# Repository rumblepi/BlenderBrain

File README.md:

# BlenderBrain

A controller for continuous flow blending of Nitrox and Trimix gases for diving.
The controller uses two oxygen sensors (one after Helium injection and one after Oxygen injection) and from this computes the composition of the resulting gas.
The desired mix can be adjusted by the user and is then automatically controlled via two magnetic valves. Depending on the currently measured mix, the valves are kept open longer or shorter. For this, a PI controller is implemented.

## Hardware

In the 'Hardware' folder, the KiCad files for the PCB are stored. Due to availability issues, the current configuration of the controller uses an Atmega168 microcontroller, but if available an Atmega328P can and should be used. The board requires two power supplies, one 5V to supply the microcontroller and operational amplifiers and a 24V to supply the magnetic valves as well as the indicator lights.

The oxygen sensors are assumed to be common rebreather sensors, namely ones similar to the NRC D-05R sensor range. These sensors expose three pins, of which we will use two to measure the output voltage. These galvanic cell sensors are dependent current sources outputting a given current for a certain oxygen partial pressure. The sensor also contains a small temperature compensation circuit with a few resistors and an NTC element, such that it effectively outputts a small voltage depending on the current oxygen partial pressure.
For more details see for example [http://www.advanceddivermagazine.com/articles/sensors/sensors.html].

As operational amplifiers, two TLC271 chips are used, but could be combined into a single TLC272 chip in the future. These OpAmps operate in non-inverting configuration with a gain of 101 and an additional feedback capacitor to filter high frequency noise. Note that only two of the three pins of the oxygen sensor are used.

### Programming the microcontroller via ISP

In-System-Programming can be used to update the firmware of the microcontroller. A detailed description of this procedure is given on the Arduino webpage (https://docs.arduino.cc/built-in-examples/arduino-isp/ArduinoISP), we store the most important points here for future reference.
We use an Arduino UNO in ISP mode to write to the Atmega microcontroller chip via the ISP pins on the board. 
Then, in the Arduino IDE the ISP sketch must be uploaded to the UNO via 'File->Examples->ArduinoISP->ArduinoISP'.

The ISP pins have a silkscreen overlay and the connections to the UNO are as follows: MOSI - 11, MISO - 12, SCK - 13, VCC - 5V, GND - GND, RESET - 10
In addition to this, it might be necessary to put a 10uF capacitor between the RESET and GND pins on the UNO.
The Atmega168 is available as processor of an Arduino Duemilanove, so in order to program it, select 'Tools->Board->Arduino Duemilanove or Dieciemila' and switch the processor to 'Atmega168' via 'Tools->Processor->Atmega168'. As we are using the UNO as an In-System-Programmer, also select 'Tools->Programmer->Arduino as ISP'. At first it might be necessary to burn a bootloader onto the chip, so select 'Tools->Burn Bootloader'. After that, the standard 'Upload'-button should do the trick.

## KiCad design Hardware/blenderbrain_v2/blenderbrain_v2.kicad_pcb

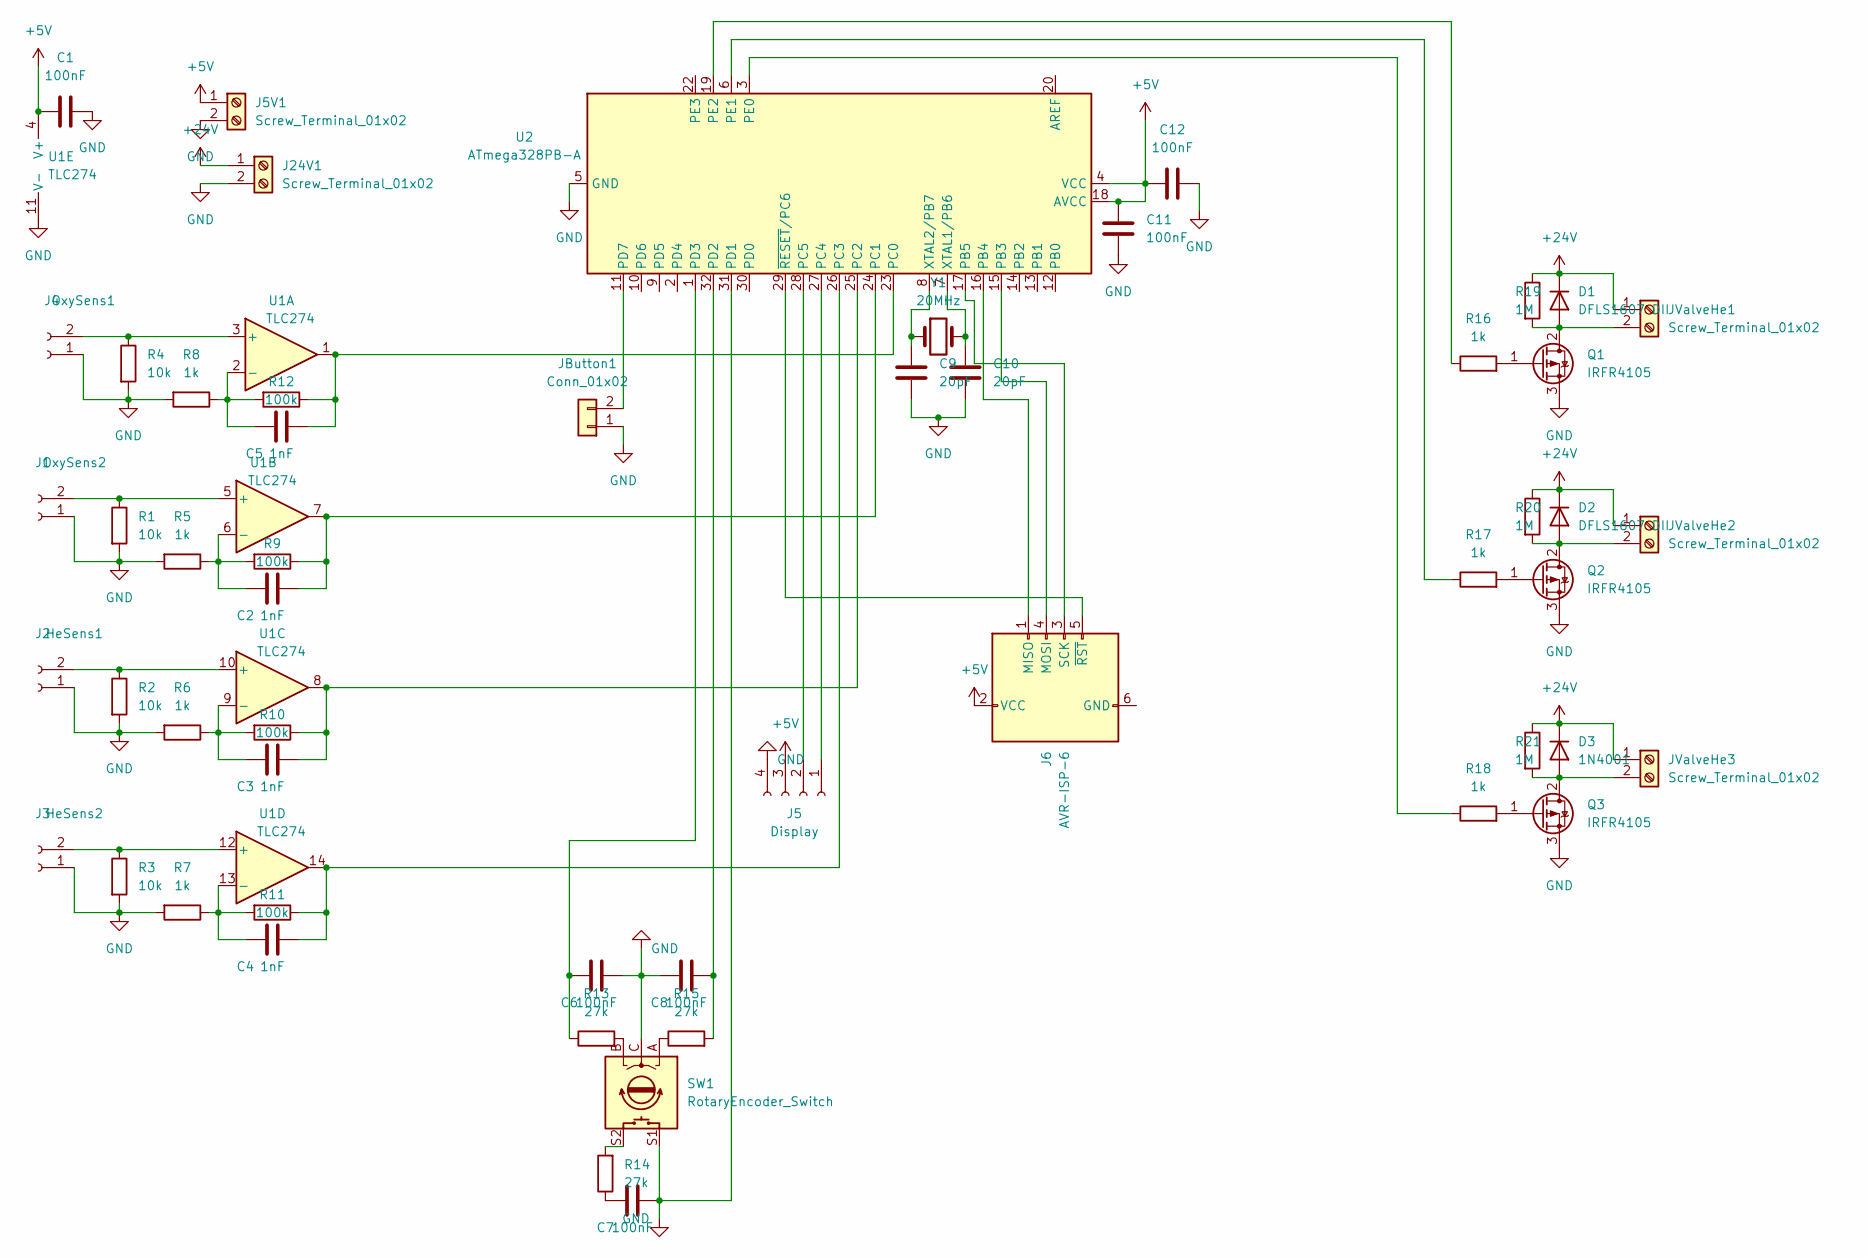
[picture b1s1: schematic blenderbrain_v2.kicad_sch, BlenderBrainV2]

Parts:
C1, C6, C7, C8, C11, C12: 100nF; C_1206_3216Metric
C2, C3, C4, C5: 1nF; C_1206_3216Metric
C9, C10: 20pF; C_1206_3216Metric
D1, D2: DFLS1607 DII; D_PowerDI-123
D3: 1N4001; D_PowerDI-123
J1: OxySens2; JST_EH_S2B-EH_1x02_P2.50mm_Horizontal
J2: HeSens1; JST_EH_S2B-EH_1x02_P2.50mm_Horizontal
J3: HeSens2; JST_EH_S2B-EH_1x02_P2.50mm_Horizontal
J4: OxySens1; JST_EH_S2B-EH_1x02_P2.50mm_Horizontal
J5: Display; PinSocket_1x04_P2.54mm_Vertical
J5V1, J24V1: Screw_Terminal_01x02; TerminalBlock_bornier-2_P5.08mm
J6: AVR-ISP-6; PinHeader_2x03_P2.54mm_Vertical
JButton1: Conn_01x02; PinHeader_1x02_P2.54mm_Vertical
JValveHe1, JValveHe2, JValveHe3: Screw_Terminal_01x02; JST_EH_B2B-EH-A_1x02_P2.50mm_Vertical
Q1, Q2, Q3: IRFR4105; TO-252-2
R1, R2, R3, R4: 10k; R_1206_3216Metric
R5, R6, R7, R8, R16, R17, R18: 1k; R_1206_3216Metric
R9, R10, R11, R12: 100k; R_1206_3216Metric
R13, R14, R15: 27k; R_1206_3216Metric
R19, R20, R21: 1M; R_1206_3216Metric
SW1: RotaryEncoder_Switch; RotaryEncoder_Alps_EC11E-Switch_Vertical_H20mm
U1: TLC274; SO-14_3.9x8.65mm_P1.27mm
U2: ATmega328PB-A; TQFP-32_7x7mm_P0.8mm
Y1: 20MHz; Crystal_HC49-U_Vertical

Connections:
+5V: C1.1, C11.2, C12.1, J5.3, J5V1.1, J6.2 (VCC), U1.4 (V+), U2.4 (VCC), U2.18 (AVCC)
+24V: D1.1 (K), D2.1 (K), D3.1 (K), J24V1.1, JValveHe1.1, JValveHe2.1, JValveHe3.1, R19.1, R20.1, R21.1
GND: C1.2, C6.2, C7.2, C8.1, C9.2, C10.2, C11.1, C12.2, J1.1, J2.1, J3.1, J4.1, J5.4, J5V1.2, J24V1.2, JButton1.1, Q1.3 (S), Q2.3 (S), Q3.3 (S), R1.2, R2.2, R3.2, R4.2, R5.2, R6.2, R7.2, R8.2, SW1.C, SW1.S1, U1.11 (V-), U2.5 (GND), U2.21 (GND), U2.31 (PD1)
unnamed: C2.1, R5.1, R9.2, U1.6 (-)
unnamed: C2.2, R9.1, U1.7, U2.24 (PC1)
unnamed: C3.1, R6.1, R10.2, U1.9 (-)
unnamed: C3.2, R10.1, U1.8, U2.25 (PC2)
unnamed: C4.1, R7.1, R11.2, U1.13 (-)
unnamed: C4.2, R11.1, U1.14, U2.26 (PC3)
unnamed: C5.1, R8.1, R12.2, U1.2 (-)
unnamed: C5.2, R12.1, U1.1, U2.23 (PC0)
unnamed: C6.1, R13.1, U2.1 (PD3)
unnamed: C7.1, R14.1
unnamed: C9.1, U2.8 (XTAL2/PB7), Y1.1
unnamed: C10.1, U2.7 (XTAL1/PB6), Y1.2
unnamed: D1.2 (A), JValveHe1.2, Q1.2 (D), R19.2
unnamed: D2.2 (A), JValveHe2.2, Q2.2 (D), R20.2
unnamed: D3.2 (A), JValveHe3.2, Q3.2 (D), R21.2
unnamed: J1.2, R1.1, U1.5 (+)
unnamed: J2.2, R2.1, U1.10 (+)
unnamed: J3.2, R3.1, U1.12 (+)
unnamed: J4.2, R4.1, U1.3 (+)
unnamed: J5.1, U2.27 (PC4)
unnamed: J5.2, U2.28 (PC5)
unnamed: J6.1 (MISO), U2.16 (PB4)
unnamed: J6.3 (SCK), U2.17 (PB5)
unnamed: J6.4 (MOSI), U2.15 (PB3)
unnamed: J6.5 (~RST), U2.29 (~RESET/PC6)
unnamed: Q1.1 (G), R16.2
unnamed: Q2.1 (G), R17.2
unnamed: Q3.1 (G), R18.2
unnamed: R13.2, SW1.B
unnamed: R14.2, SW1.S2
unnamed: R15.1, SW1.A
unnamed: R16.1, U2.19 (PE2)
unnamed: R17.1, U2.6 (PE1)
unnamed: R18.1, U2.3 (PE0)
unnamed: JButton1.2, U2.11 (PD7)
unnamed: C8.2, R15.2, U2.32 (PD2)

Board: 2 copper layers, 55 parts (0 on the bottom side), 39 nets, no tracks yet.

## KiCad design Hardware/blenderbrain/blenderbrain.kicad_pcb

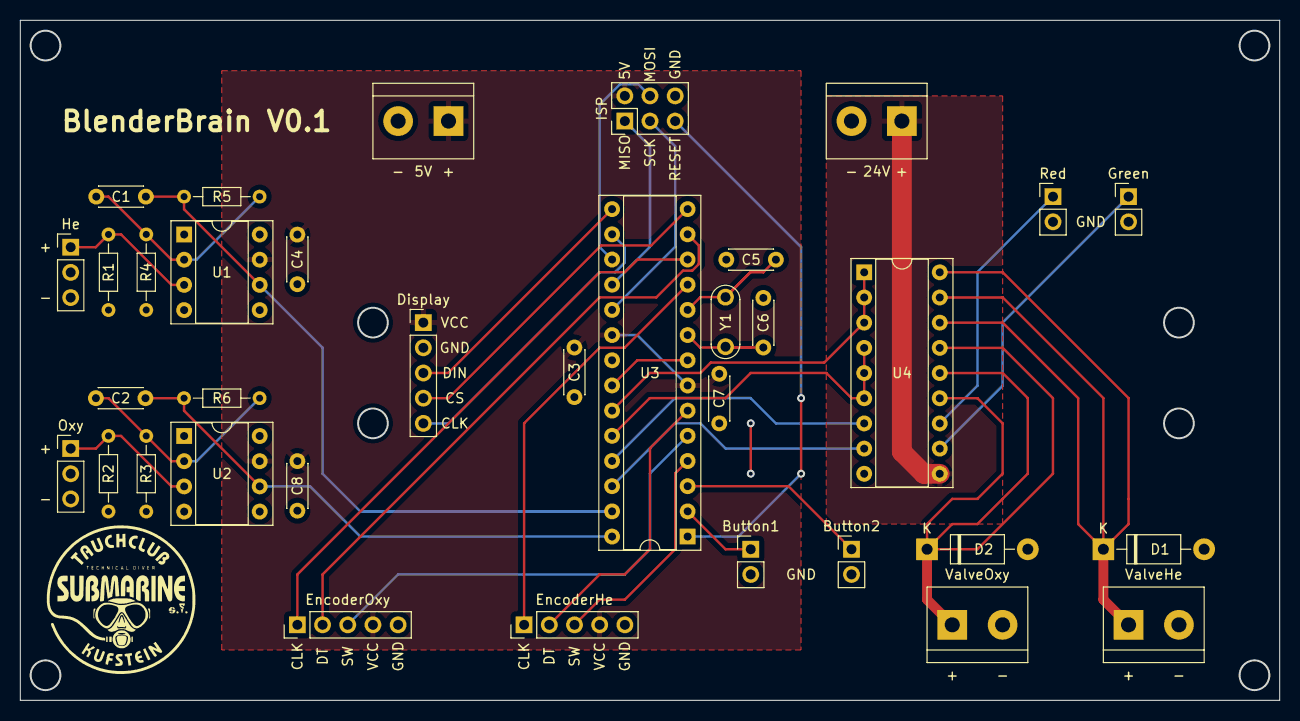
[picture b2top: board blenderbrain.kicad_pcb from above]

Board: 2 copper layers, 126.9 x 68.5 mm, 35 parts (0 on the bottom side), 34 nets.

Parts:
5V, 24V: Screw_Terminal_01x02; TerminalBlock_bornier-2_P5.08mm
Button1, Button2: Conn_01x02; PinHeader_1x02_P2.54mm_Vertical
C1, C2: 1nF; C_Disc_D4.3mm_W1.9mm_P5.00mm
C3, C4, C7, C8: 100nF; C_Disc_D4.3mm_W1.9mm_P5.00mm
C5, C6: 20pF; C_Disc_D4.3mm_W1.9mm_P5.00mm
D1, D2: 1N4001; D_DO-41_SOD81_P10.16mm_Horizontal
Display: Conn_01x05_Male; PinHeader_1x05_P2.54mm_Vertical
EncoderHe: Conn_01x05_Male; PinHeader_1x05_P2.54mm_Vertical
EncoderOxy: Conn_01x05_Male; PinHeader_1x05_P2.54mm_Vertical
Green: Conn_01x02; PinHeader_1x02_P2.54mm_Vertical
He: Conn_He; PinHeader_1x03_P2.54mm_Vertical
ISP: AVR-ISP-6; PinHeader_2x03_P2.54mm_Vertical
Oxy: Conn_Oxy; PinHeader_1x03_P2.54mm_Vertical
R1, R2: 10k; R_Axial_DIN0204_L3.6mm_D1.6mm_P7.62mm_Horizontal
R3, R4: 1k; R_Axial_DIN0204_L3.6mm_D1.6mm_P7.62mm_Horizontal
R5, R6: 100k; R_Axial_DIN0204_L3.6mm_D1.6mm_P7.62mm_Horizontal
Red: Conn_01x02; PinHeader_1x02_P2.54mm_Vertical
U1, U2: OP177GPZ; DIP-8_W7.62mm_Socket
U3: ATmega168-20P; DIP-28_W7.62mm_Socket
U4: ULN2803A; DIP-18_W7.62mm_Socket
ValveHe: Screw_Terminal_01x02; TerminalBlock_bornier-2_P5.08mm
ValveOxy: Screw_Terminal_01x02; TerminalBlock_bornier-2_P5.08mm
Y1: 10MHz; Resonator-2Pin_W7.0mm_H2.5mm

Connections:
+5V: 5V.1, C3.1, C4.1, C7.2, C8.1, Display.1, EncoderHe.4, EncoderOxy.4, ISP.2 (VCC), U1.7 (V+), U2.7 (V+), U3.7 (VCC), U3.20 (AVCC)
+24V: 24V.1, U4.10 (COM)
GND: 5V.2, 24V.2, Button1.2, Button2.2, C3.2, C4.2, C5.2, C6.2, C7.1, C8.2, D1.2 (A), D2.2 (A), Display.2, EncoderHe.5, EncoderOxy.5, Green.2, He.3, ISP.6 (GND), Oxy.3, R1.2, R2.2, R3.2, R4.2, Red.2, U1.4 (V-), U2.4 (V-), U3.8 (GND), U3.22 (GND), U4.9 (GND), ValveHe.2, ValveOxy.2
unnamed: C1.1, R4.1, R5.2, U1.2 (-IN)
unnamed: C1.2, R5.1, U1.6 (OUT), U3.27 (PC4)
unnamed: C2.1, R3.1, R6.2, U2.2 (-IN)
unnamed: C2.2, R6.1, U2.6 (OUT), U3.28 (PC5)
unnamed: C5.1, U3.10 (XTAL2/PB7), Y1.1
unnamed: C6.1, U3.9 (XTAL1/PB6), Y1.2
unnamed: D1.1 (K), U4.16 (O3), U4.17 (O2), U4.18 (O1), ValveHe.1
unnamed: D2.1 (K), U4.13 (O6), U4.14 (O5), U4.15 (O4), ValveOxy.1
unnamed: He.1, R1.1, U1.3 (+IN)
unnamed: Oxy.1, R2.1, U2.3 (+IN)
unnamed: ISP.1 (MISO), U3.18 (PB4)
unnamed: ISP.3 (SCK), U3.19 (PB5)
unnamed: ISP.4 (MOSI), U3.17 (PB3)
unnamed: ISP.5 (~RST), U3.1 (~RESET/PC6)
unnamed: Button1.1, U3.2 (PD0)
unnamed: Button2.1, U3.3 (PD1)
unnamed: Display.3, U3.15 (PB1)
unnamed: Display.4, U3.14 (PB0)
unnamed: Display.5, U3.16 (PB2)
unnamed: EncoderHe.1, U3.11 (PD5)
unnamed: EncoderHe.2, U3.6 (PD4)
unnamed: EncoderHe.3, U3.4 (PD2)
unnamed: EncoderOxy.1, U3.12 (PD6)
unnamed: EncoderOxy.2, U3.13 (PD7)
unnamed: EncoderOxy.3, U3.5 (PD3)
unnamed: Green.1, U4.11 (O8)
unnamed: Red.1, U4.12 (O7)
unnamed: U3.23 (PC0), U4.1 (I1), U4.2 (I2), U4.3 (I3)
unnamed: U3.24 (PC1), U4.4 (I4), U4.5 (I5), U4.6 (I6)
unnamed: U3.25 (PC2), U4.7 (I7)
unnamed: U3.26 (PC3), U4.8 (I8)

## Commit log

2022-11-17 Added first version of hardware design
2022-11-17 Added main control file with used pinout and included first libraries
2022-11-18 Added prototype encoder support
2022-11-19 Added He-Encoder and Oxygen sensor, introduced Machine States
2022-11-20 Changed UI for the first few steps and added a debounced button struct
2022-11-20 Added a simple PID control structure
2022-11-22 Dropped the differential term in the control and added clipping
2022-11-25 Added debugging option and some todos for cleaning up the code
2022-11-30 Added several structs encapsulating previously global methods.
2022-11-30 Added todos for the next hardware version
2022-12-02 Fixed the main methods and deleted some needlessly difficult UI handling
2022-12-03 Fixed encoder bounce by using a state based method
2022-12-03 Added second oxygen sensor to compute the helium content of the mix
2022-12-03 Added v2 idea
2022-12-04 Added MagneticValve and StatusLed classes
2022-12-13 Added some documetation
2023-03-28 added clear method to main control
2023-03-28 Added alternative version for UI and some improvements to the code structure
2023-03-29 Added menu items
2023-03-30 Finished basic UI
2023-03-31 tidied up filestructure
2023-03-31 fixed some display issues and added calibration after reset
2023-04-01 added constraints for he and oxy depending on previous settings
2023-04-09 Added valve control
2023-04-09 added set menu
2023-04-09 fixup: debouncer construction in valve control
2023-04-09 Removed status led
2023-04-29 removed 'set' entry at startup
2023-04-29 removed mainmenu and added 'go' option to mix setup
2023-04-30 show the deviation from the average mix up to now to the user
2023-05-26 fixed visualization and reset of estimated mix
2023-05-27 Create LICENSE
2023-05-27 Added userdoc
2023-08-29 chore: added .gitignor for backup files
2023-08-29 feat: added v2 schematic
2023-09-01 hardware: added rotary encoder to pcb and made first alignment
